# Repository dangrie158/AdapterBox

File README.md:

# Adapter Box

A simple multiconnector Adapter Box to hopefully fulfill all connection needs. It features 2 Channels (e.g. +/-) and the following connectors:

- 1x 5.5mm / 2.1mm DC-Jack (center positive)
- 1x USB-A
- 1x Phoenix Contact MKDSN Screw Terminals (0.2" / 5.08mm Pitch)
- 4x (2 per Channel) 4mm Banana Jack
- 4x (2 per Channel) 6.3mm Spade Terminal Connector
- 2x (1 per Channel) 5.5mm / 6.3mm Contact Point (e.g. for Crocodile Clips)
- 1x BNC (vertical mounting)
- 12x (6 per Channel) Female Pinheader (0.1" / 2,57mm Pitch)
- 12x (6 per Channel) Male Pinheader (0.1" / 2,57mm Pitch)
- 1x Power LED

The Power LED is driven my an LM334 constant current source that can handle up to 40V and 20V in reverse polarity. If you plan on going any higher, don't populate the components.

## Renders
### Assembly

### Board
#### Topside:

#### Bottomside:

### BOM
For a Spreadsheet BOM, see [BOM.xlsx](BOM.xlsx).

The full BOM is currently only available from CONRAD Electronic, however for most Parts you should be able to easily find a replacement (see the Spreadsheet for some Digikey Part#s). Only the Case could be a bit hard to find elsewhere, but it is not mandatory to have (make one from Acrylic sheets for example).

|                    | Qty | Manufacturer      | Manufacturer Part No. | Order-No.    | Price (1) | Price (10) | Extended Price (1) |
|--------------------|-----|-------------------|-----------------------|--------------|-----------|------------|--------------------|
| BNC Jack           | 1   | TRU-Components    | 730413                | 1566143 - 62 | 3,44      | 3,24       | 3,44               |
| Case               | 1   | TRU-Components    | TC-2024 SW203         | 1588559 - 62 | 2,86      | 2,74       | 2,86               |
| Connector Straight | 4   | TE Connectivity   | 726386-2              | 808428 - 62  | 0,21      | 0,19       | 0,84               |
| Connector Bridge   | 2   | Vogt              | 1098a.68              | 739844 - 62  | 0,09      | 0,08       | 0,18               |
| Pinheader Female   | 2   | Connfly           | 1498356               | 1498356 - 62 | 0,12      | 0,09       | 0,24               |
| Pinheader Male     | 2   | Connfly           | 1390113               | 1390113 - 62 | 0,12      | 0,09       | 0,24               |
| Contact Plug       | 1   | Phoenix Contact   | 1758018               | 743603 - 62  | 0,42      | 0,41       | 0,42               |
| USB-A              | 1   | econ-connect      | USBBUVA               | 1311468 - 62 | 0,91      | 0,85       | 0,91               |
| Contact Screw      | 1   | Phoenix Contact   | 1729018               | 743530 - 62  | 0,54      | 0,52       | 0,54               |
| Banana Jack Black  | 2   | Schützinger       | BU 403 sz             | 737657 - 62  | 1,3       | 1,18       | 2,6                |
| Banana Jack Red    | 2   | Schützinger       | BU 403 rt             | 737672 - 62  | 1,3       | 1,18       | 2,6                |
| DC Jack            | 1   | TRU-Components    | 1582643               | 1582643 - 62 | 0,68      | 0,62       | 0,68               |
| LM334              | 1   | Texas Instruments | LM334M/NOPB           | 1014051 - 62 | 0,65      | 0,58       | 0,65               |
| 36 Ohm 0603        | 1   | Samsung           | RC1608F36R0CS         | 436455 - 62  | 0,02      | 0,02       | 0,02               |
| 100 Ohm 0603       | 1   | TRU-Components    | 1585242               | 1585242 - 62 | 0,02      | 0,02       | 0,02               |
| BC807              | 1   | Nexperia          | BC807-25,215          | 1112884 - 62 | 0,2       | 0,19       | 0,2                |
| Power LED          | 1   | Kingbright        | L 53 LID              | 146005 - 62  | 0,13      | 0,12       | 0,13               |
|                    |     |                   |                       |              |           |            |                    |
|                    |     |                   |                       |              |           | **Total**  | **16,2**           |

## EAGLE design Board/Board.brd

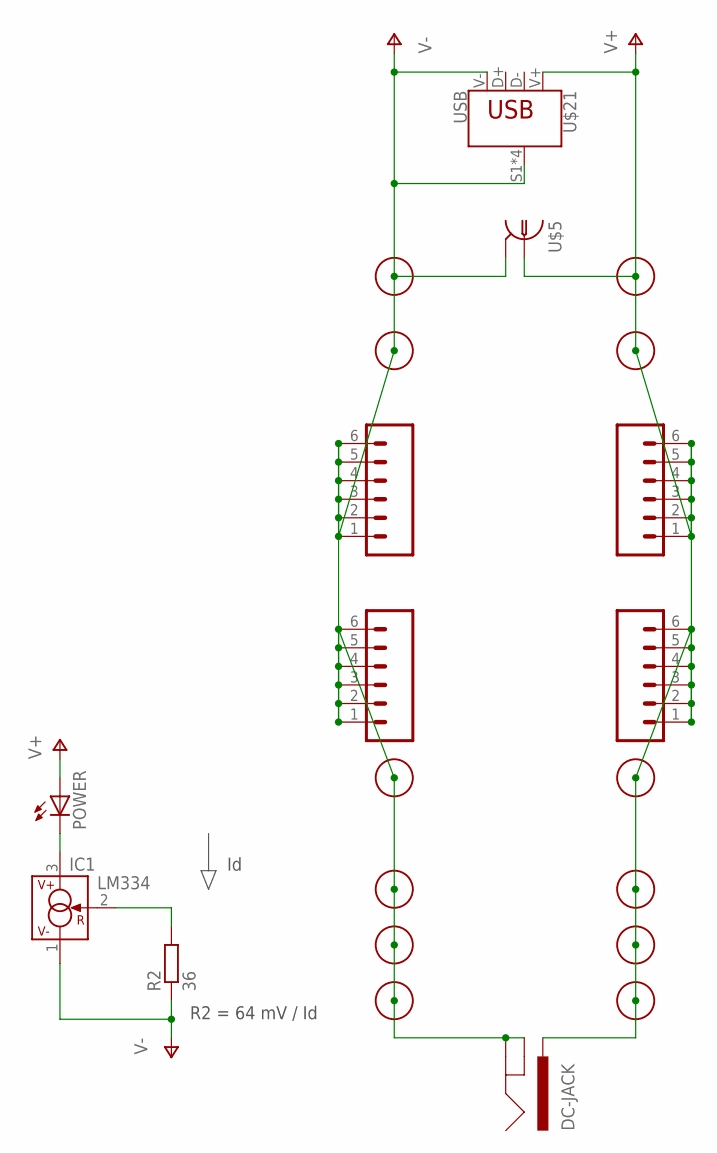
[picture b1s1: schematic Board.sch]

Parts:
IC1: LM334; SO08
POWER: LED5MM
R2: 36; R0603
U$1, U$3: 6MM-BANANA-PLUGSCREW-BLACK; 6MM-TERMINAL-POST-BLACK
U$2, U$4: 6MM-BANANA-PLUGSCREW-RED; 6MM-TERMINAL-POST-RED
U$5: BNC-VTE-1-1337541-0; BNC-V
U$6, U$7: PINHEADER-1X6MALE_LOCK; 1X06_LOCK
U$8, U$9: PINHEADER-1X6FEMALE_LOCK; 1X06_FEMALE_LOCK.010
U$10: TERMINAL-BLOCK-2; MKDSN1,5/2-5,08
U$12: DC-JACK; POWER_JACK_PTH
U$14, U$15, U$18, U$19: TERMINAL-1; TE-726386
U$16, U$17: TERMINAL-1BRIDGE; VOGT-1098A.68
U$21: USB; ECON-USBBUVA

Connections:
unnamed: IC1.2 (R), R2.2
unnamed: IC1.3 (V+), POWER.K (C)
V+: POWER.A, U$2.P$1, U$4.P$1, U$5.CONDUCTOR1 (C), U$7.1, U$7.2, U$7.3, U$7.4, U$7.5, U$7.6, U$9.1, U$9.2, U$9.3, U$9.4, U$9.5, U$9.6, U$10.1, U$12.PWR, U$15.P$1, U$15.P$2, U$16.P$1, U$16.P$2, U$19.P$1, U$19.P$2, U$21.V+ (VBUS)
V-: IC1.1 (V-), R2.1, U$1.P$1, U$3.P$1, U$5.CONDUCTOR2 (S), U$5.SHIELD1 (S), U$5.SHIELD2 (S), U$6.1, U$6.2, U$6.3, U$6.4, U$6.5, U$6.6, U$8.1, U$8.2, U$8.3, U$8.4, U$8.5, U$8.6, U$10.2, U$12.GND, U$12.GNDBREAK, U$14.P$1, U$14.P$2, U$17.P$1, U$17.P$2, U$18.P$1, U$18.P$2, U$21.S1 (SHIELD), U$21.S2 (SHIELD), U$21.S3 (SHIELD), U$21.S4 (SHIELD), U$21.V- (GND)

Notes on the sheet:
R2 = 64 mV / Id

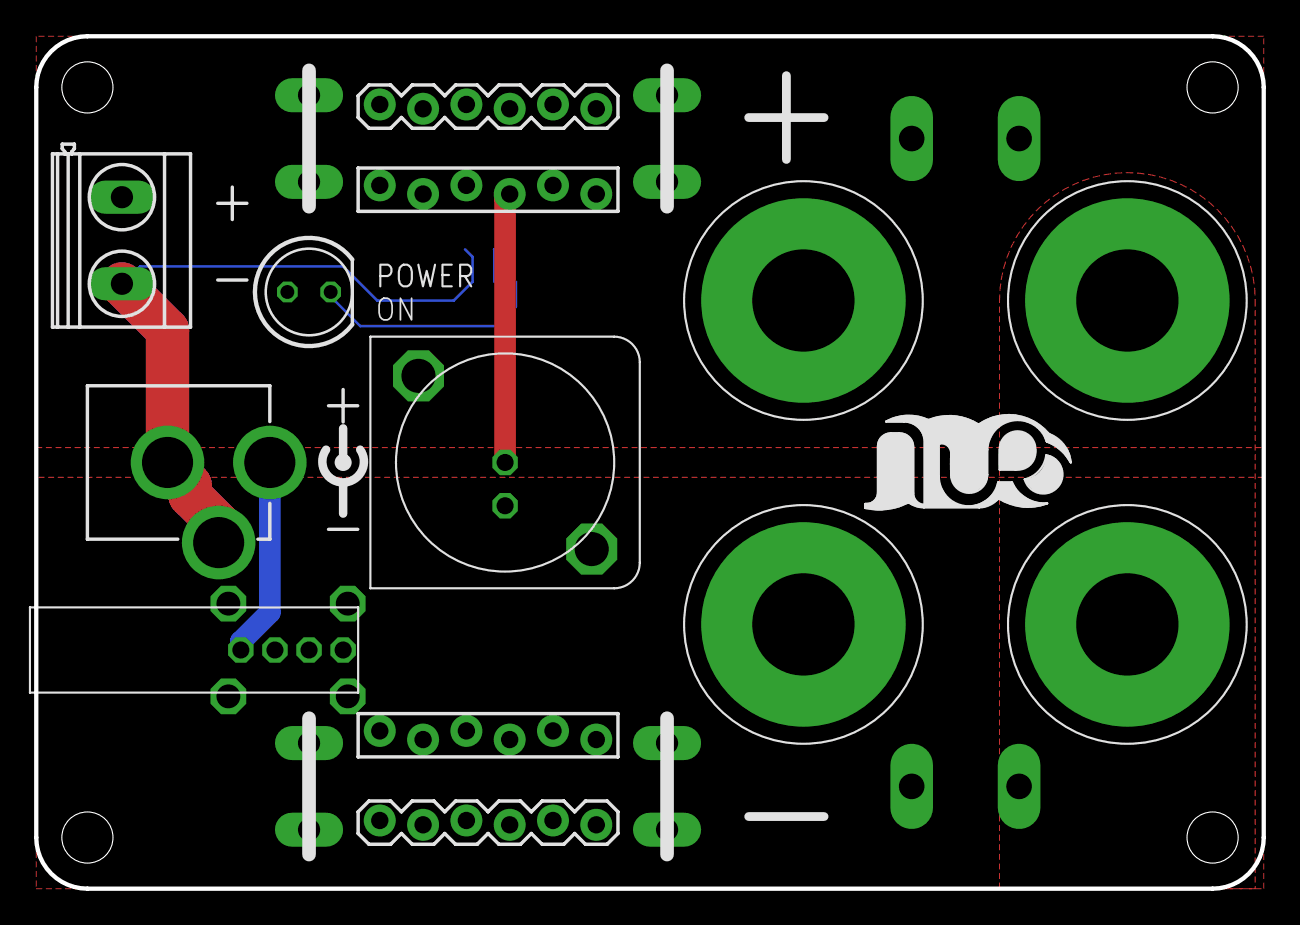
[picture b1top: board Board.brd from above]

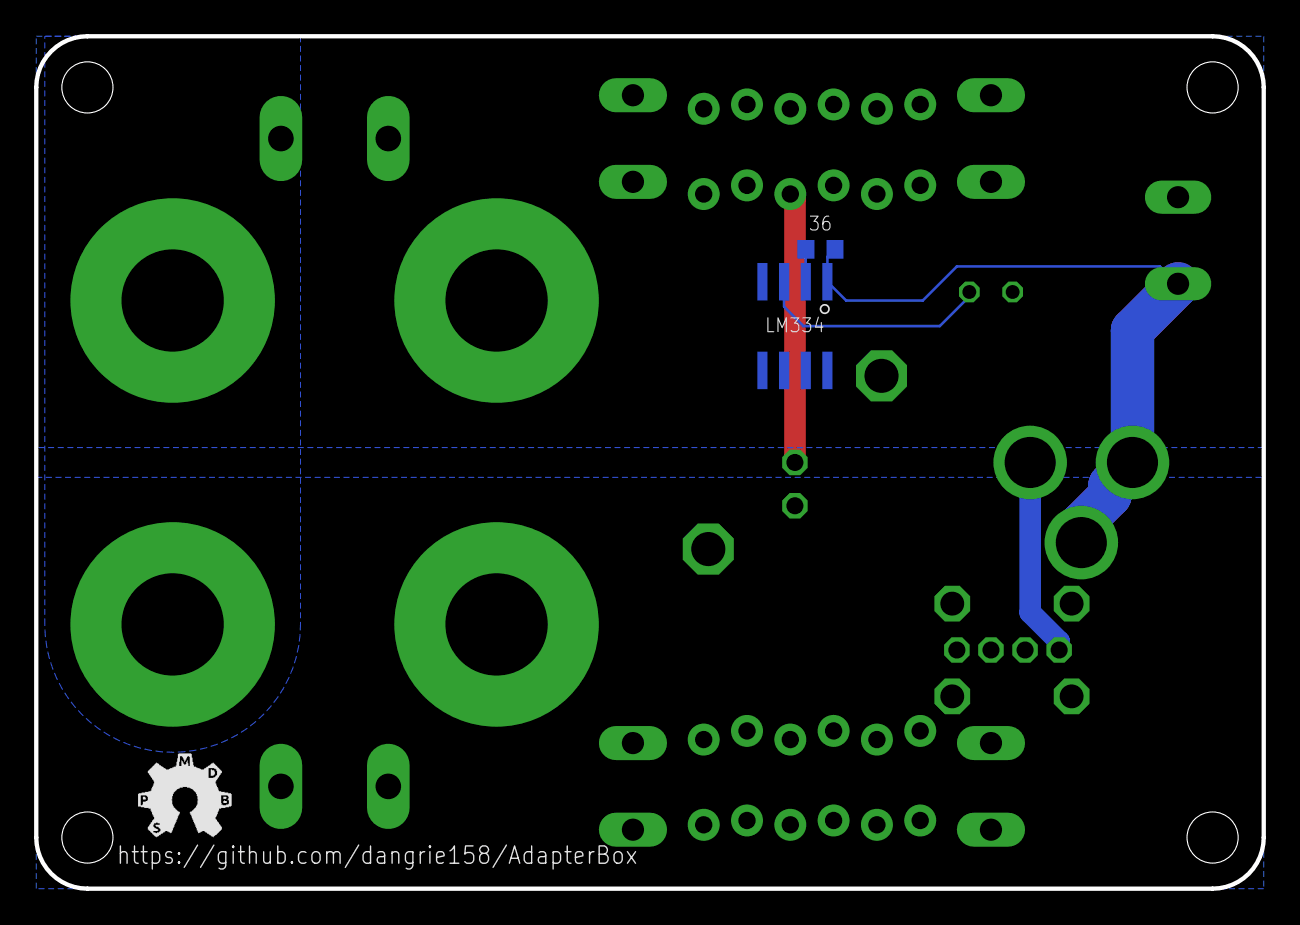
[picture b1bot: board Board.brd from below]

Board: 2 copper layers, 72.0 x 50.0 mm, 22 parts (2 on the bottom side), 4 nets.

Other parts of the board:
U$13: LOGO-SILKSCREEN

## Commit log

2018-11-10 added Board File
2018-11-10 added PDFs for Board Layout
2018-11-10 added current Gerbers
2018-11-10 added BOM
2018-11-10 added Excel Backup files to gitignore
2018-11-10 added README
2018-11-10 fixed layout error in README BOM table
2018-11-10 moved BNC to center for better access to lower profile connectors
2018-11-12 implemented various suggestions from the forum post
2018-11-12 updated renders and production gerbers to latest version
2018-11-12 updated BOM and README
2018-11-19 fixed BNC pinout
2018-12-01 updated BNC footprint
2018-12-01 updated pinheader 3d models
2018-12-09 increased constant current feedback resistor
2019-01-01 reverted to old bnc footprint
2019-01-01 added pin 1 marker for lm334
2019-01-01 added LED to BOM
2019-01-01 updated gerbers and PDFs with new version
2019-01-17 Updated badge link
2019-01-17 updated constant current source for power LED
